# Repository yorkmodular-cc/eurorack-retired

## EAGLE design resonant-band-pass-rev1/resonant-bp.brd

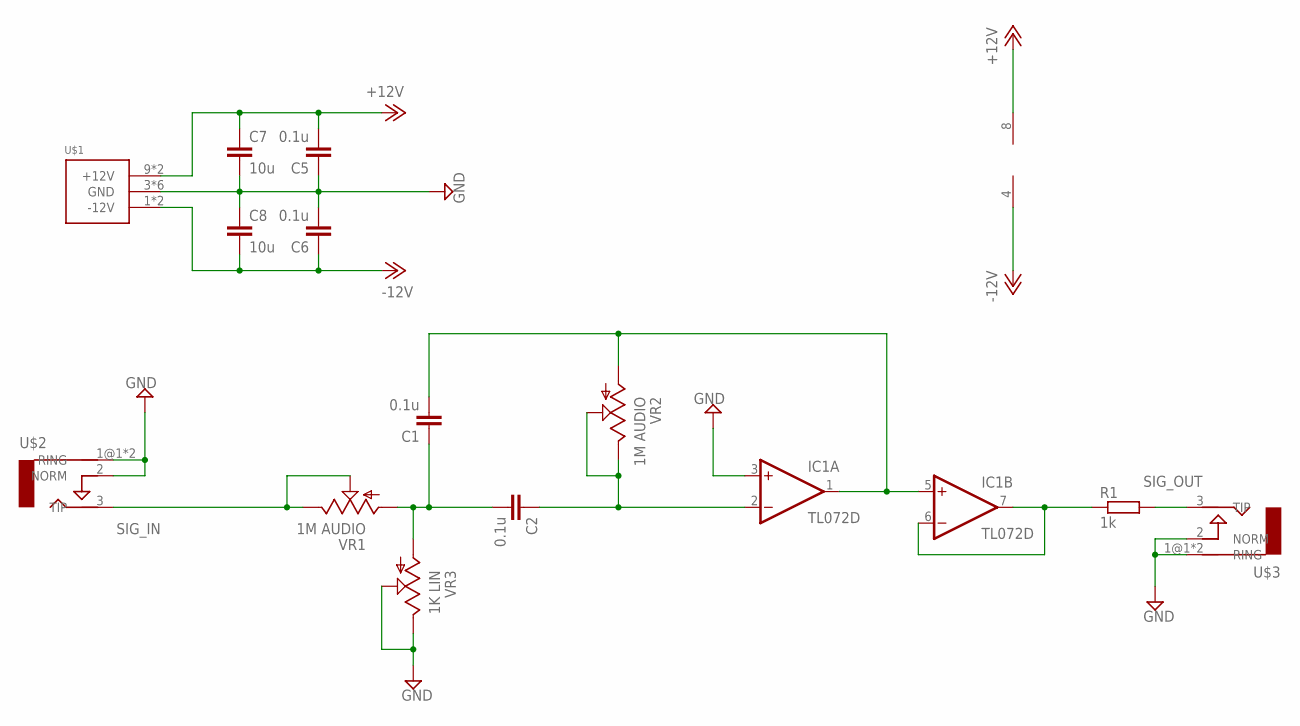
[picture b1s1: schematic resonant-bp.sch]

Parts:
C1, C2, C5, C6: 0.1u; C0805
C7, C8: 10u; C0805
IC1: TL072D; SO08
R1: 1k; R0805
U$1: POWER_SIMPLE10; POWER_10
U$2, U$3: AUDIO-JACKERTHENVAR; ERTHENVAR-JACK
VR1, VR2: 1M AUDIO; 9MM_SNAP-IN_POT
VR3: 1K LIN; 9MM_SNAP-IN_POT

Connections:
+12V: C5.2, C7.1, IC1.8 (V+), U$1.9 (+12V), U$1.10 (+12V)
-12V: C6.1, C8.2, IC1.4 (V-), U$1.1 (-12V), U$1.2 (-12V)
GND: C5.1, C6.2, C7.2, C8.1, IC1.3 (+IN), U$1.3 (GND), U$1.4 (GND), U$1.5 (GND), U$1.6 (GND), U$1.7 (GND), U$1.8 (GND), U$2.1@1 (RING), U$2.1@2 (RING), U$2.2 (NORM), U$3.1@1 (RING), U$3.1@2 (RING), U$3.2 (NORM), VR3.2 (S), VR3.3 (E)
unnamed: C1.1, C2.2, VR1.1 (A), VR3.1 (A)
unnamed: C1.2, IC1.1 (OUT), IC1.5 (+IN), VR2.1 (A)
unnamed: C2.1, IC1.2 (-IN), VR2.2 (S), VR2.3 (E)
unnamed: IC1.6 (-IN), IC1.7 (OUT), R1.1
SIG_IN: U$2.3 (TIP), VR1.2 (S), VR1.3 (E)
SIG_OUT: R1.2, U$3.3 (TIP)

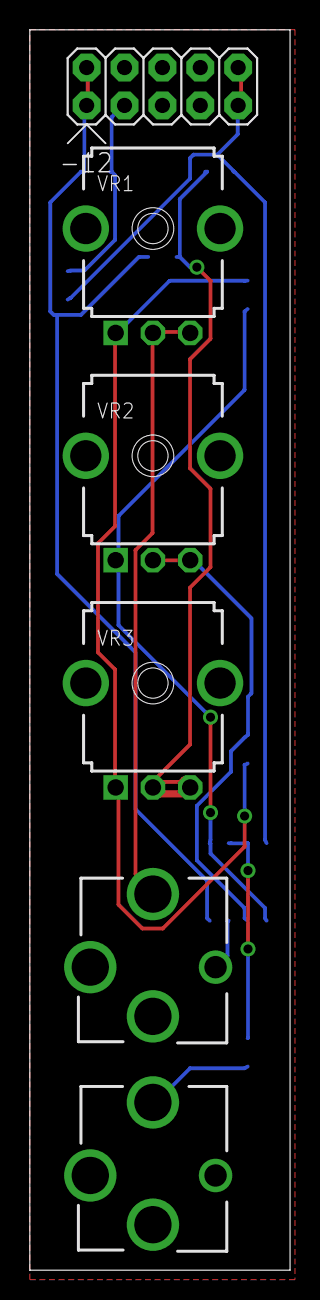
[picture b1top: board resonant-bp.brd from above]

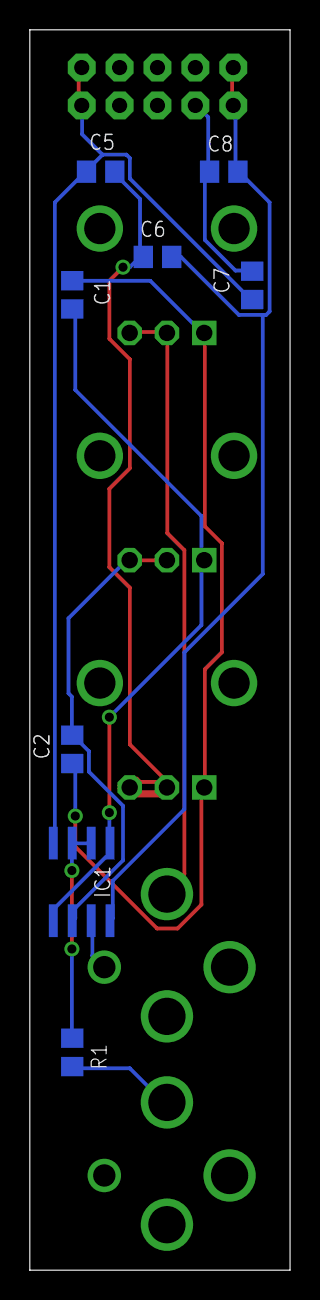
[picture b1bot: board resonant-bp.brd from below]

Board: 2 copper layers, 17.4 x 83.2 mm, 14 parts (8 on the bottom side), 9 nets.

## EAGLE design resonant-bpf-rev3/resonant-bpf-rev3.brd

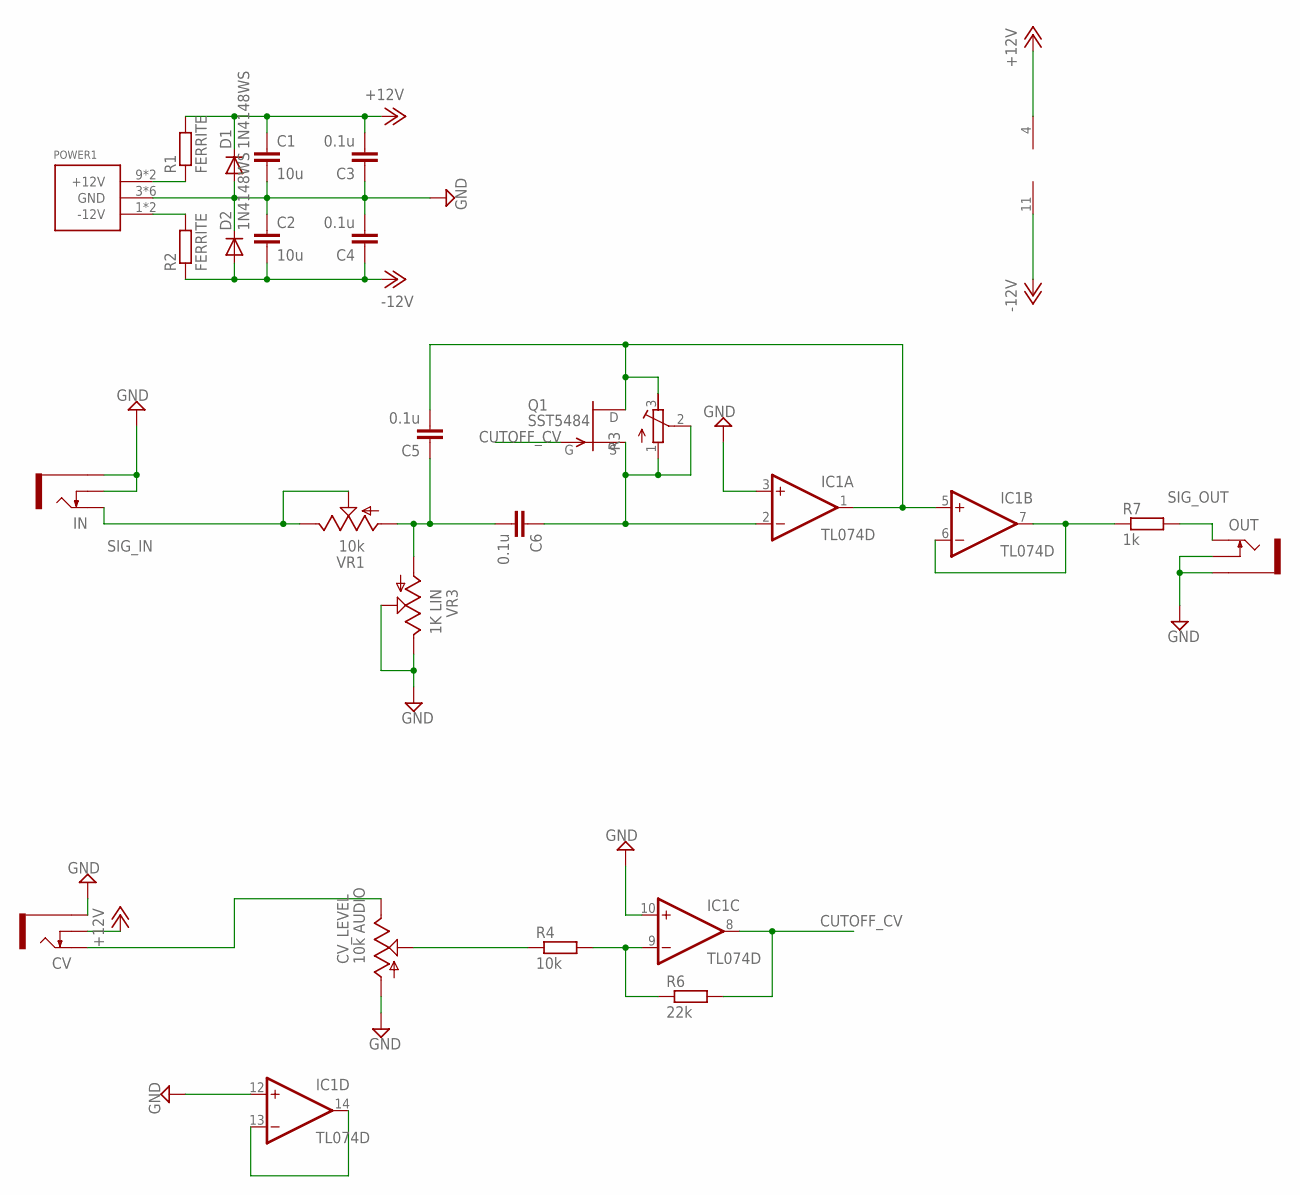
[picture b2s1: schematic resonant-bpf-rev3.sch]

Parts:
C1, C2: 10u; C0805
C3, C4, C5, C6: 0.1u; C0805
CV: THONKICONNNEW; WQP-PJ301M-12_JACK
CV_LEVEL: 10k AUDIO; 9MM_SNAP-IN_POT
D1, D2: 1N4148WS; SOD323-W
IC1: TL074D; SO14
IN: THONKICONNNEW; WQP-PJ301M-12_JACK
OUT: THONKICONNNEW; WQP-PJ301M-12_JACK
POWER1: POWER_SIMPLE10; POWER_10
Q1: SST5484; SOT23
R1, R2: FERRITE; R0805
R3: R-TRIMM3296W; RTRIM3296W
R4: 10k; R0805
R6: 22k; R0805
R7: 1k; R0805
VR1: 10k; 9MM_SNAP-IN_POT
VR3: 1K LIN; 9MM_SNAP-IN_POT

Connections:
+12V: C1.1, C3.2, CV.P$2_SWITCH (SWITCH), D1.C, IC1.4 (V+), R1.2
-12V: C2.2, C4.1, D2.A, IC1.11 (V-), R2.1
CUTOFF_CV: IC1.8 (OUT), Q1.3 (G), R6.2
GND: C1.2, C2.1, C3.1, C4.2, CV.P$3_SLEEVE (SLEEVE), CV_LEVEL.1 (A), D1.A, D2.C, IC1.3 (+IN), IC1.10 (+IN), IC1.12 (+IN), IN.P$2_SWITCH (SWITCH), IN.P$3_SLEEVE (SLEEVE), OUT.P$2_SWITCH (SWITCH), OUT.P$3_SLEEVE (SLEEVE), POWER1.3 (GND), POWER1.4 (GND), POWER1.5 (GND), POWER1.6 (GND), POWER1.7 (GND), POWER1.8 (GND), VR3.2 (S), VR3.3 (E)
unnamed: C5.1, C6.2, VR1.1 (A), VR3.1 (A)
unnamed: POWER1.1 (-12V), POWER1.2 (-12V), R2.2
unnamed: POWER1.9 (+12V), POWER1.10 (+12V), R1.1
unnamed: C5.2, IC1.1 (OUT), IC1.5 (+IN), Q1.1 (D), R3.3 (E)
unnamed: C6.1, IC1.2 (-IN), Q1.2 (S), R3.1 (A), R3.2 (S)
unnamed: CV.P$1_TIP (TIP), CV_LEVEL.3 (E)
unnamed: CV_LEVEL.2 (S), R4.1
unnamed: IC1.9 (-IN), R4.2, R6.1
unnamed: IC1.6 (-IN), IC1.7 (OUT), R7.1
unnamed: IC1.13 (-IN), IC1.14 (OUT)
SIG_IN: IN.P$1_TIP (TIP), VR1.2 (S), VR1.3 (E)
SIG_OUT: OUT.P$1_TIP (TIP), R7.2

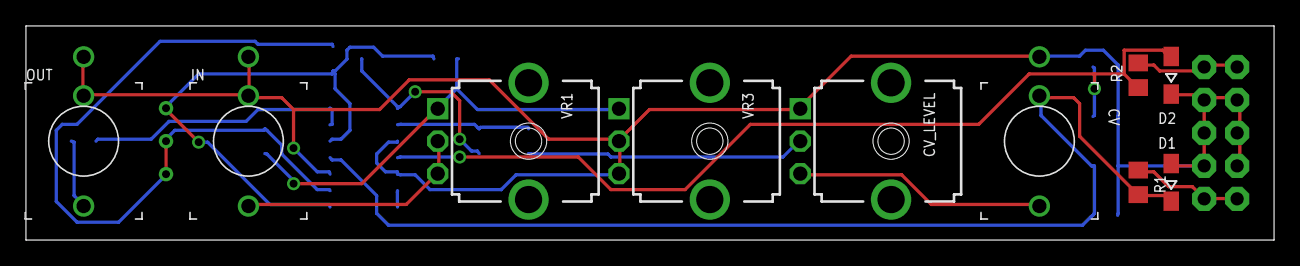
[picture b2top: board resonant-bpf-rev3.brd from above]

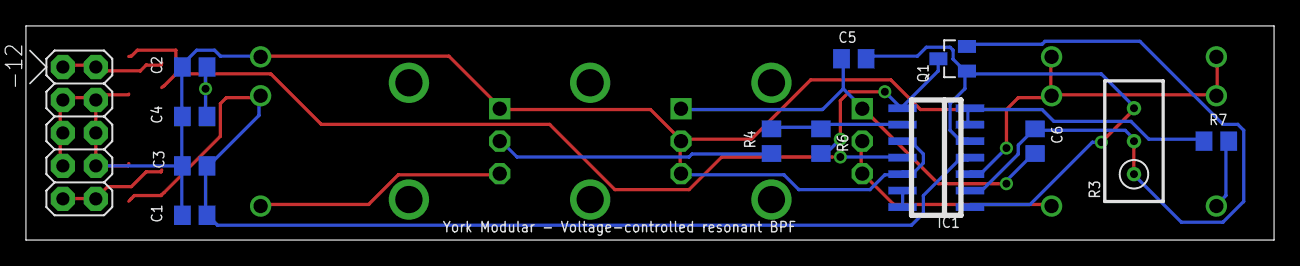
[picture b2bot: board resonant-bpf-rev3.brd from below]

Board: 2 copper layers, 96.2 x 16.5 mm, 23 parts (13 on the bottom side), 16 nets.

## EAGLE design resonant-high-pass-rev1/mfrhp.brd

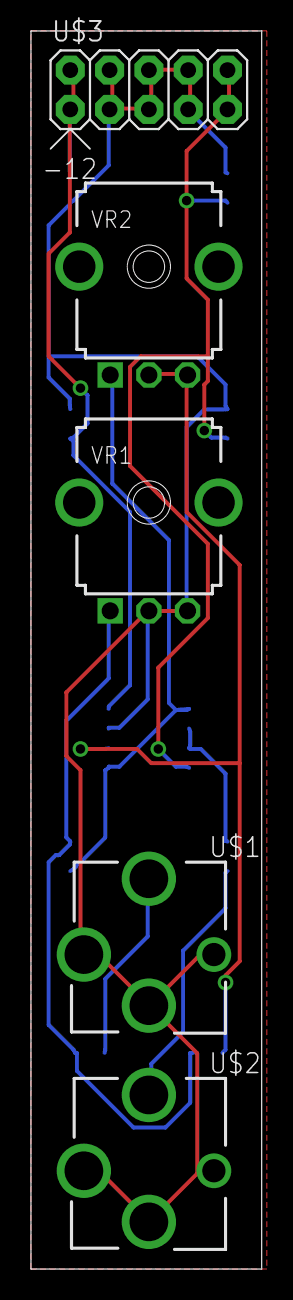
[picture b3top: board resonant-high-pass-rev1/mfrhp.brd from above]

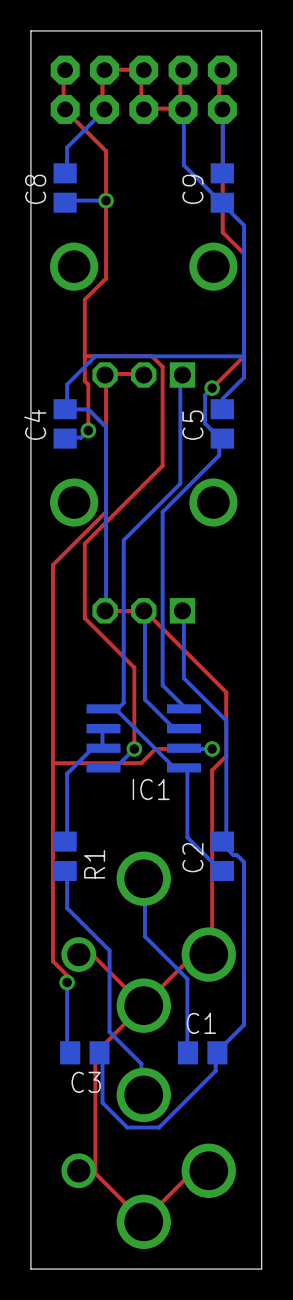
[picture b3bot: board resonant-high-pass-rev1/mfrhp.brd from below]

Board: 2 copper layers, 14.9 x 80.0 mm, 14 parts (9 on the bottom side), 9 nets.

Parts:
C1, C2, C3, C4, C5: 0.1u; C0805
C8, C9: 10u; C0805
IC1: TL072D; SO08
R1: 1k; R0805
U$1, U$2: AUDIO-JACKERTHENVAR; ERTHENVAR-JACK
U$3: POWER_SIMPLE10; POWER_10
VR1: 1k; 9MM_SNAP-IN_POT
VR2: 1M; 9MM_SNAP-IN_POT

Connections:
+12V: C4.1, C8.1, IC1.8, U$3.9, U$3.10
-12V: C5.1, C9.2, IC1.4, U$3.1, U$3.2
GND: C4.2, C5.2, C8.2, C9.1, IC1.3, U$1.1@1, U$1.1@2, U$1.2, U$2.1@1, U$2.1@2, U$2.2, U$3.3, U$3.4, U$3.5, U$3.6, U$3.7, U$3.8, VR1.2, VR1.3
IN: C1.1, U$1.3
unnamed: C3.2, IC1.2, VR2.2, VR2.3
unnamed: C1.2, C2.2, C3.1, VR1.1
unnamed: IC1.6, IC1.7, R1.1
unnamed: C2.1, IC1.1, IC1.5, VR2.1
OUT: R1.2, U$2.3

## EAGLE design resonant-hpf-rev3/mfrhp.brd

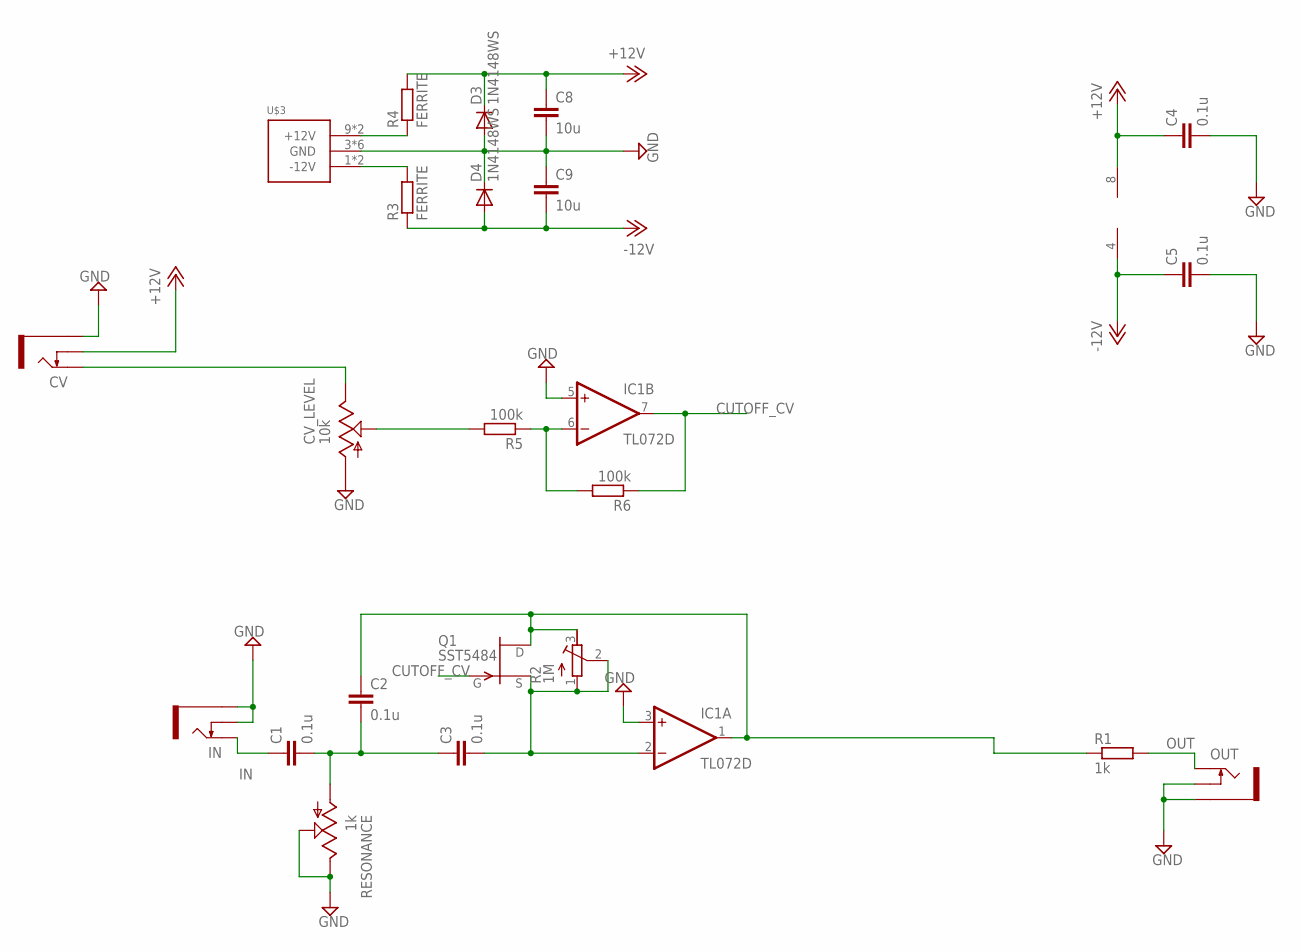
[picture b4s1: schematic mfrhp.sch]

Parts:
C1, C2, C3, C4, C5: 0.1u; C0805
C8, C9: 10u; C0805
CV: THONKICONNNEW; WQP-PJ301M-12_JACK
CV_LEVEL: 10k; 9MM_SNAP-IN_POT
D3, D4: 1N4148WS; SOD323-W
IC1: TL072D; SO08
IN: THONKICONNNEW; WQP-PJ301M-12_JACK
OUT: THONKICONNNEW; WQP-PJ301M-12_JACK
Q1: SST5484; SOT23
R1: 1k; R0805
R2: 1M; RTRIM3296W
R3, R4: FERRITE; R0805
R5, R6: 100k; R0805
RESONANCE: 1k; 9MM_SNAP-IN_POT
U$3: POWER_SIMPLE10; POWER_10

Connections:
+12V: C4.1, C8.1, CV.P$2_SWITCH (SWITCH), D3.C, IC1.8 (V+), R4.2
-12V: C5.1, C9.2, D4.A, IC1.4 (V-), R3.1
CUTOFF_CV: IC1.7 (OUT), Q1.3 (G), R6.1
GND: C4.2, C5.2, C8.2, C9.1, CV.P$3_SLEEVE (SLEEVE), CV_LEVEL.1 (A), D3.A, D4.C, IC1.3 (+IN), IC1.5 (+IN), IN.P$2_SWITCH (SWITCH), IN.P$3_SLEEVE (SLEEVE), OUT.P$2_SWITCH (SWITCH), OUT.P$3_SLEEVE (SLEEVE), RESONANCE.2 (S), RESONANCE.3 (E), U$3.3 (GND), U$3.4 (GND), U$3.5 (GND), U$3.6 (GND), U$3.7 (GND), U$3.8 (GND)
IN: C1.1, IN.P$1_TIP (TIP)
unnamed: R3.2, U$3.1 (-12V), U$3.2 (-12V)
unnamed: C3.2, IC1.2 (-IN), Q1.2 (S), R2.1 (A), R2.2 (S)
unnamed: C1.2, C2.2, C3.1, RESONANCE.1 (A)
unnamed: R4.1, U$3.9 (+12V), U$3.10 (+12V)
unnamed: IC1.6 (-IN), R5.1, R6.2
unnamed: CV_LEVEL.2 (S), R5.2
unnamed: CV.P$1_TIP (TIP), CV_LEVEL.3 (E)
unnamed: C2.1, IC1.1 (OUT), Q1.1 (D), R1.1, R2.3 (E)
OUT: OUT.P$1_TIP (TIP), R1.2

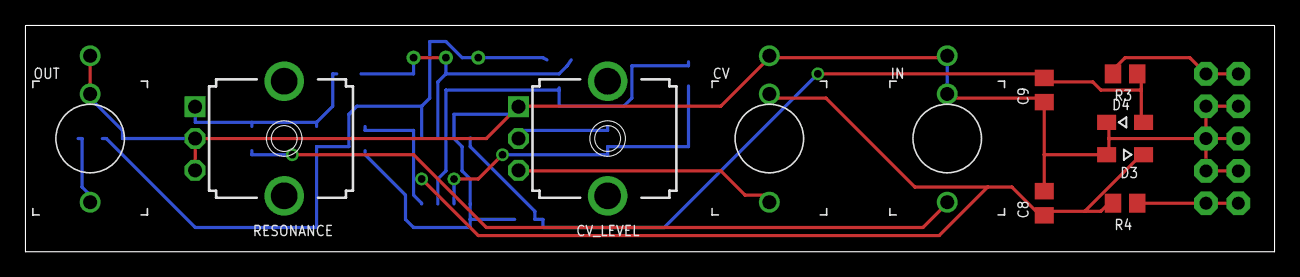
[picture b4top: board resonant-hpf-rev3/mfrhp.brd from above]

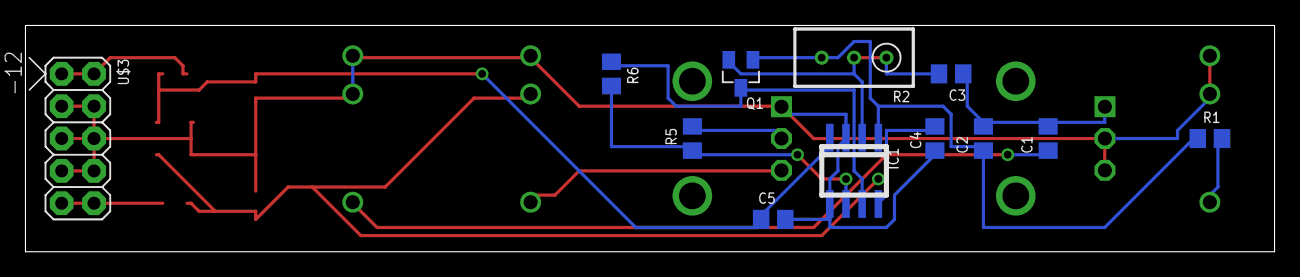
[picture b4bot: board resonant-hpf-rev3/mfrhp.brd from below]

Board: 2 copper layers, 98.1 x 17.8 mm, 23 parts (12 on the bottom side), 14 nets.

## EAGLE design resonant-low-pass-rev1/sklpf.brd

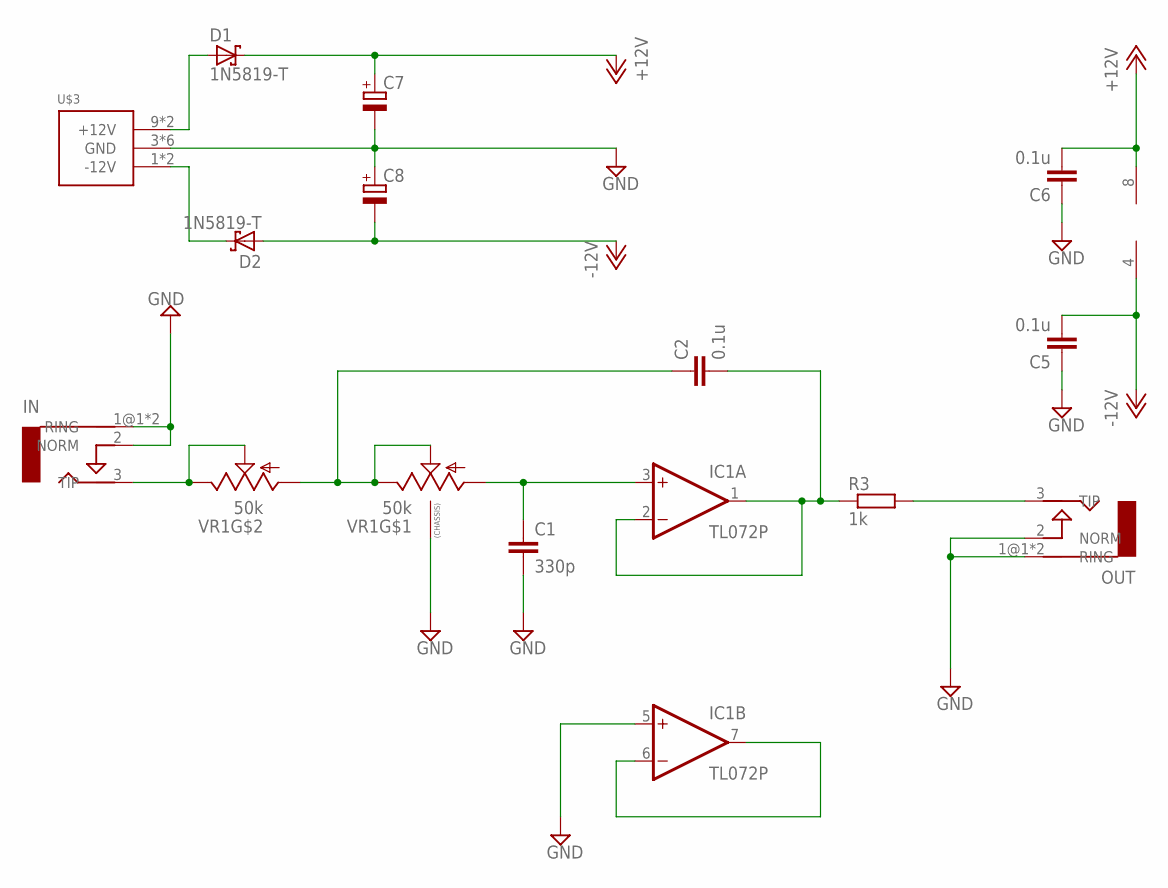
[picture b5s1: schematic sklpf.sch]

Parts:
C1: 330p; C025-025X050
C2: 0.1u; C050-025X075
C5, C6: 0.1u; C025-025X050
C7, C8: CPOL-EUE2,5-6E; E2,5-6E
D1, D2: 1N5819-T; DO41-7.6
IC1: TL072P; DIL08
IN: AUDIO-JACKERTHENVAR; ERTHENVAR-JACK
OUT: AUDIO-JACKERTHENVAR; ERTHENVAR-JACK
R3: 1k; 0207/2V
U$3: POWER_SIMPLE10; POWER_10
VR1: 50k; DUAL_9MM_SNAP-IN_POT

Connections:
+12V: C6.2, C7.+, D1.C, IC1.8 (V+)
-12V: C5.2, C8.-, D2.A, IC1.4 (V-)
GND: C1.2, C5.1, C6.1, C7.-, C8.+, IC1.5 (+IN), IN.1@1 (RING), IN.1@2 (RING), IN.2 (NORM), OUT.1@1 (RING), OUT.1@2 (RING), OUT.2 (NORM), U$3.3 (GND), U$3.4 (GND), U$3.5 (GND), U$3.6 (GND), U$3.7 (GND), U$3.8 (GND), VR1.CHASSIS1, VR1.CHASSIS2
unnamed: C2.2, IC1.1 (OUT), IC1.2 (-IN), R3.1
unnamed: C1.1, IC1.3 (+IN), VR1.1 (A)
unnamed: C2.1, VR1.1B (A), VR1.2 (S), VR1.3 (E)
unnamed: IN.3 (TIP), VR1.2B (S), VR1.3B (E)
unnamed: IC1.6 (-IN), IC1.7 (OUT)
unnamed: OUT.3 (TIP), R3.2
unnamed: D2.C, U$3.1 (-12V), U$3.2 (-12V)
unnamed: D1.A, U$3.9 (+12V), U$3.10 (+12V)

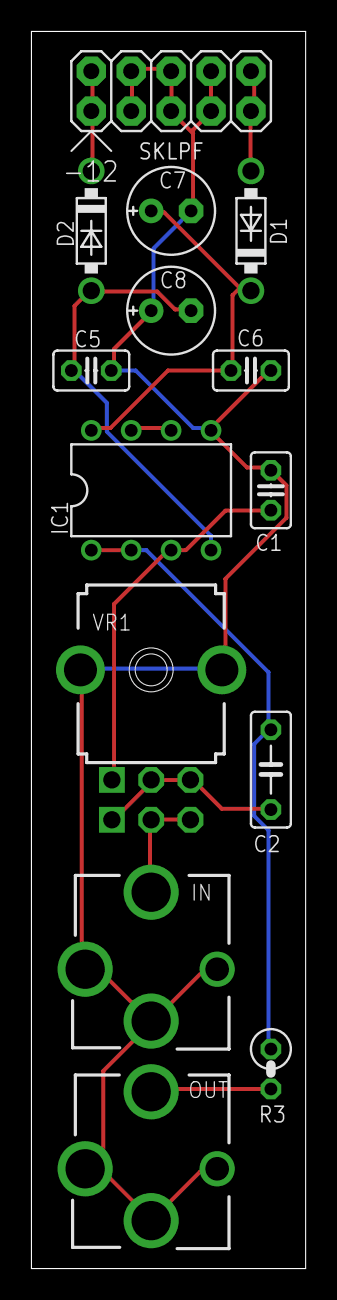
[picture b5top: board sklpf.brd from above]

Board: 2 copper layers, 17.4 x 78.7 mm, 14 parts (0 on the bottom side), 11 nets.
